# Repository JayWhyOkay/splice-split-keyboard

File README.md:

# Splice - A Split Alice

*Splice* is a split keyboard in the Alice layout. 

The goal is to design a board suited for myself as there are no boards designed quite like the Alice. Most split boards are generally based on an ortholinear layout, something that I personally canntot get used to. 

The keyboard is based off [the Sofle Keyboard from Josef](https://github.com/josefadamcik/SofleKeyboard), with adjustments made to fit the preferred layout. 

Notes: Revision 1 and 2 PCB uses CFTKB and Sofle footprints, and all credits for footprints used belong to the respective footprint designer. 

## Images

Below are images of renders and prototypes. 

Complete project will come soon. 

Prototype of Revision 1

## Changelist

### Revision 3:
- TBA
- Normal and stepped caps support
- 2U, 2.25U spacebar support on left side
- indicator LEDs?

### Revision 2: 
- Shortened PCB dimensions 
- Relocated TRRS connector to top towards MCU Port
- Readjusted OLED Breakout 
- Added silkscreen logos for the board

## Future Changes and To-Do List
- Refactor schematics to support ai03 footprints
- make an Atmega32u4 version
- 2024: Update to latest QMK version!

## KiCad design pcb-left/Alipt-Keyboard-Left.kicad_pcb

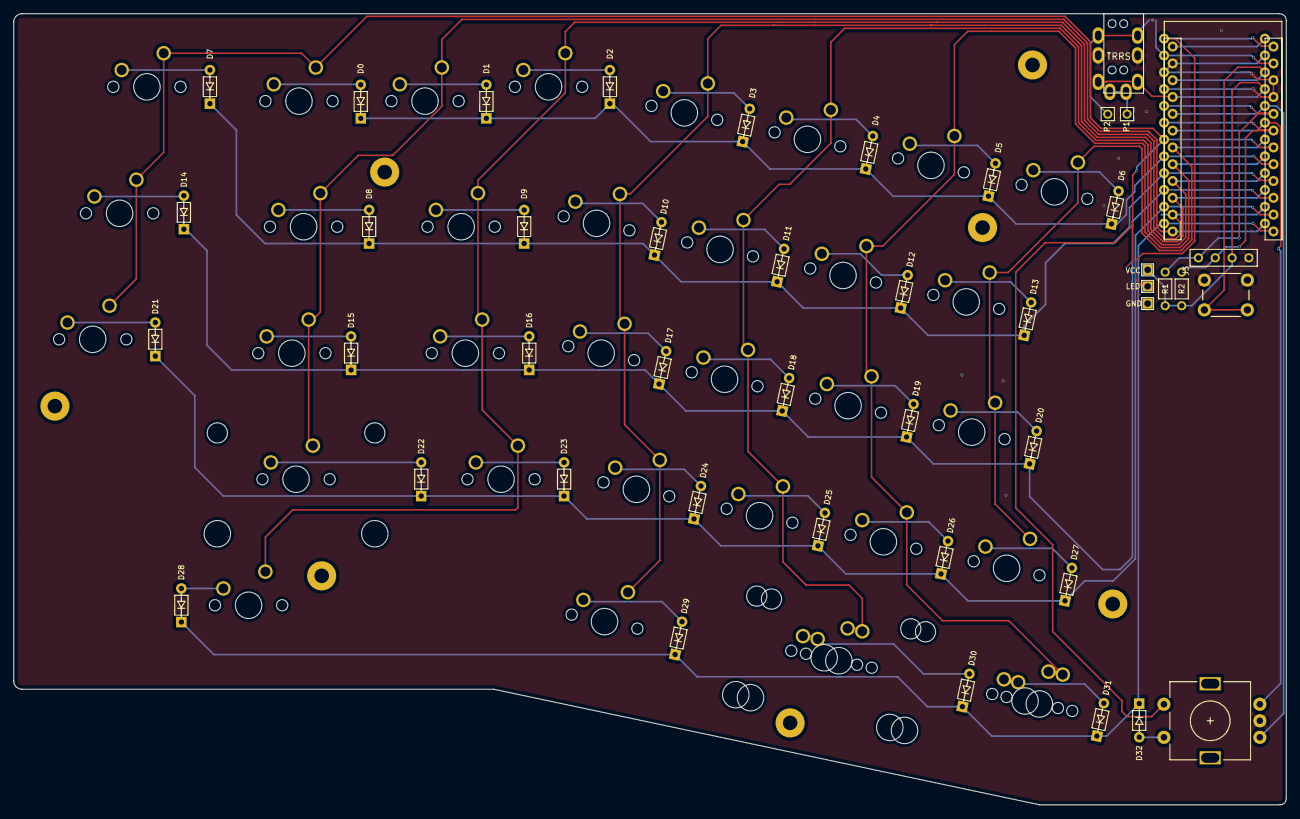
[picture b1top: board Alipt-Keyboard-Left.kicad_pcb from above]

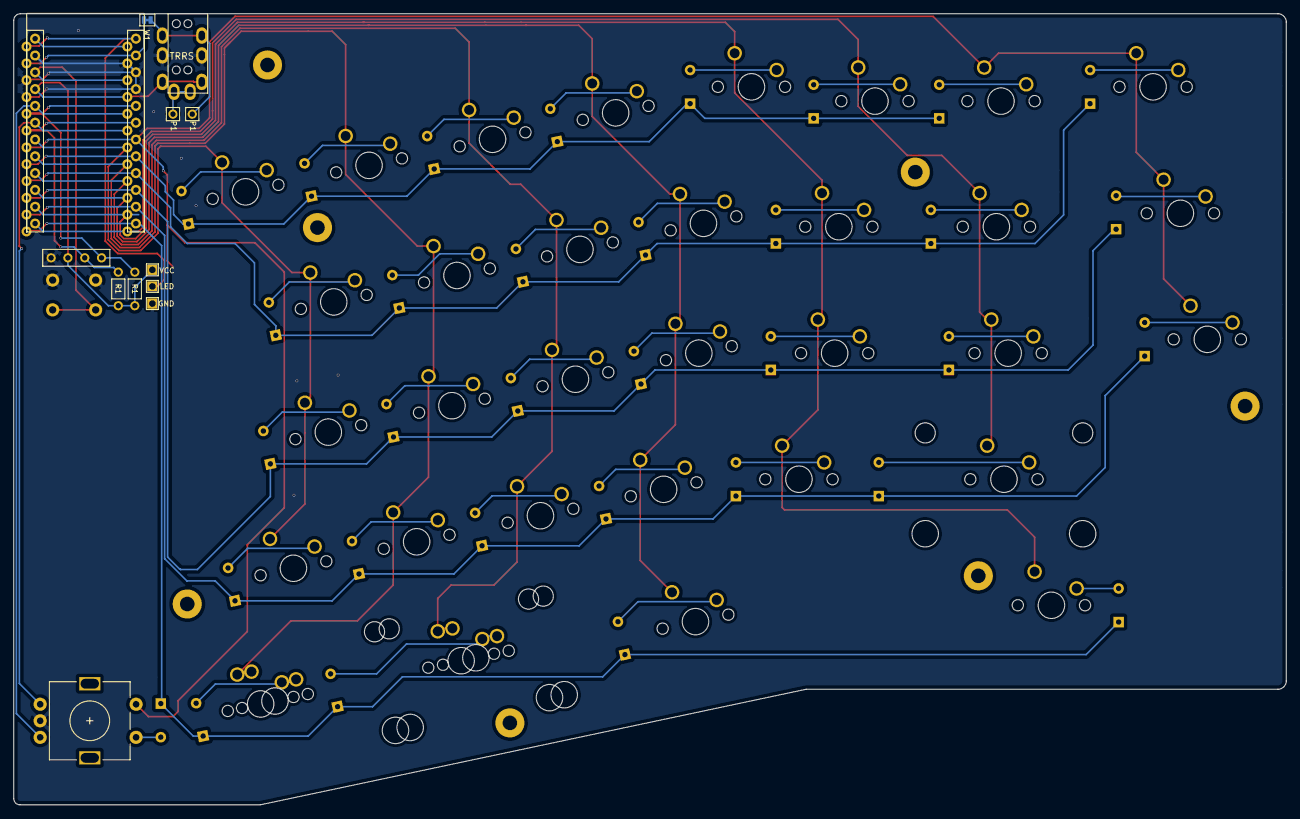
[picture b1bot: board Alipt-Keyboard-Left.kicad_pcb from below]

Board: 2 copper layers, 192.3 x 119.6 mm, 85 parts (2 on the bottom side), 56 nets.

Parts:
D0, D1, D2, D3, D4, D5, D6, D7, D8, D9, D10, D11, D12, D13, D14, D15, D16, D17, D18, D19, D20, D21, D22, D23, D24, D25, D26, D27, D28, D29, D30, D31, D32: D; D_DO-35_SOD27_P5.08mm_Horizontal
J1: LED
J2: 4PIN; MJ-4PP-9
J3: OLED; OLED_4Pin
P1, P2: i2c_pin; 1pin_conn
R1, R2: R; RESISTOR_mini
RSW1: SW_RST; SW_PUSH_6mm
SW0, SW1, SW2, SW3, SW4, SW5, SW6, SW7, SW9, SW10, SW11, SW12, SW13, SW14, SW16, SW17, SW18, SW19, SW20, SW21, SW23, SW24, SW25, SW26, SW27, SW31: SW_PUSH; SW_Cherry_MX1A_1.00u_PCB-NOSCREEN
SW8, SW28, SW29: SW_PUSH; SW_Cherry_MX1A_1.50u_PCBNOSCREEN
SW15: SW_PUSH; SW_Cherry_MX1A_1.75u_PCBNOSCREEN
SW22, SW30: SW_PUSH; SW_Cherry_MX1A_2.25u_PCBNOSCREEN
SW32: Rotary_Encoder_Switch; RotaryEncoder_Alps_EC11E-Switch_Vertical_H20mm-keebio_modif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
SW302: SW_PUSH; SW_Cherry_MX1A_2.00u_PCBNOSCREEN
SW312: SW_PUSH; SW_Cherry_MX1A_1.25u_PCBNOSCREEN
TH1, TH2, TH3, TH4, TH5, TH6, TH7: HOLE; MountingHole_2.2mm_M2_Pad
U1: ProMicro
W1: jumper; jumper_data

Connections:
/i2c_c: J2.4, P1.1
/i2c_d: J2.3, P2.1, W1.2
DATA: U1.2, W1.1
ENCA: SW32.A, U1.20
ENCB: SW32.B, U1.19
GND: J1.3, J2.2, J3.4, RSW1.1, SW32.C, U1.3, U1.4, U1.23
LED: J1.2, U1.1
unnamed: D0.2, SW0.2
unnamed: D1.2, SW1.2
unnamed: D2.2, SW2.2
unnamed: D3.2, SW3.2
unnamed: D4.2, SW4.2
unnamed: D5.2, SW5.2
unnamed: D6.2, SW6.2
unnamed: D7.2, SW7.2
unnamed: D8.2, SW8.2
unnamed: D9.2, SW9.2
unnamed: D10.2, SW10.2
unnamed: D11.2, SW11.2
unnamed: D12.2, SW12.2
unnamed: D13.2, SW13.2
unnamed: D14.2, SW14.2
unnamed: D15.2, SW15.2
unnamed: D16.2, SW16.2
unnamed: D17.2, SW17.2
unnamed: D18.2, SW18.2
unnamed: D19.2, SW19.2
unnamed: D20.2, SW20.2
unnamed: D21.2, SW21.2
unnamed: D22.2, SW22.2
unnamed: D23.2, SW23.2
unnamed: D24.2, SW24.2
unnamed: D25.2, SW25.2
unnamed: D26.2, SW26.2
unnamed: D27.2, SW27.2
unnamed: D28.2, SW28.2
unnamed: D29.2, SW29.2
unnamed: D30.2, SW30.2, SW302.2
unnamed: D31.2, SW31.2, SW312.2
RESET: RSW1.2, U1.22
SCL: J3.2, R2.2, U1.6
SDA: J3.1, R1.2, U1.5
SW32A: SW0.1, SW7.1, SW14.1, SW21.1, SW32.S1, U1.7
SW32B: D32.2, SW32.S2
VCC: J1.1, J2.1, J3.3, R1.1, R2.1, U1.21
col0: SW6.1, SW13.1, SW20.1, SW27.1, U1.18
col1: SW5.1, SW12.1, SW19.1, SW26.1, SW31.1, SW312.1, U1.17
col2: SW4.1, SW11.1, SW18.1, SW25.1, SW30.1, SW302.1, U1.16
col3: SW3.1, SW10.1, SW17.1, SW24.1, SW29.1, U1.15
col4: SW2.1, SW9.1, SW16.1, SW23.1, SW28.1, U1.14
col5: SW1.1, SW8.1, SW15.1, SW22.1, U1.13
row0: D0.1, D1.1, D2.1, D3.1, D4.1, D5.1, D6.1, U1.8
row1: D7.1, D8.1, D9.1, D10.1, D11.1, D12.1, D13.1, U1.9
row2: D14.1, D15.1, D16.1, D17.1, D18.1, D19.1, D20.1, U1.10
row3: D21.1, D22.1, D23.1, D24.1, D25.1, D26.1, D27.1, U1.11
row4: D28.1, D29.1, D30.1, D31.1, D32.1, U1.12

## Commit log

2020-07-22 Layout and beginning of wire traces for left side
2020-07-22 Layout started for right side
2020-08-20 revision 1 complete pcbs
2020-09-17 Revision 2 PCB Changes
2020-09-17 Near finalization of revision 1
2020-09-17 Refactoring
